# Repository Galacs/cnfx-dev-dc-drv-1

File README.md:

# CNFX Dev DC Driver 1

Dual 5V 1.5A DC motor driver for the cnfx series

## IC List

- STM32F103C8T6 (Main MCU)
- HT7533 (MCU 3v3 LDO)
- SN65HVD230DR (CAN transceiver)
- WS2812B (RGB addressable led)
- TPS259472 (+5V input efuse)
- DRV8837 (Integrated H-Bridge)

## Top preview

## Preview 3d render

## Pin definitions

```c

#define CAN_TX_PIN PA12
#define CAN_RX_PIN PA11
#define CAN_STATUS_PIN PA15

#define RGB_PIN PB13
#define ILM_PIN PB0
#define BTN_PIN PB12

#define SEL_0_PIN PB5
#define SEL_1_PIN PB6
#define SEL_2_PIN PB7

#define DC_1_SLEEP PA5
#define DC_1_IN1 PA6
#define DC_1_IN2 PA7

#define DC_1_SLEEP PA0
#define DC_1_IN1 PA1
#define DC_1_IN2 PA2
```

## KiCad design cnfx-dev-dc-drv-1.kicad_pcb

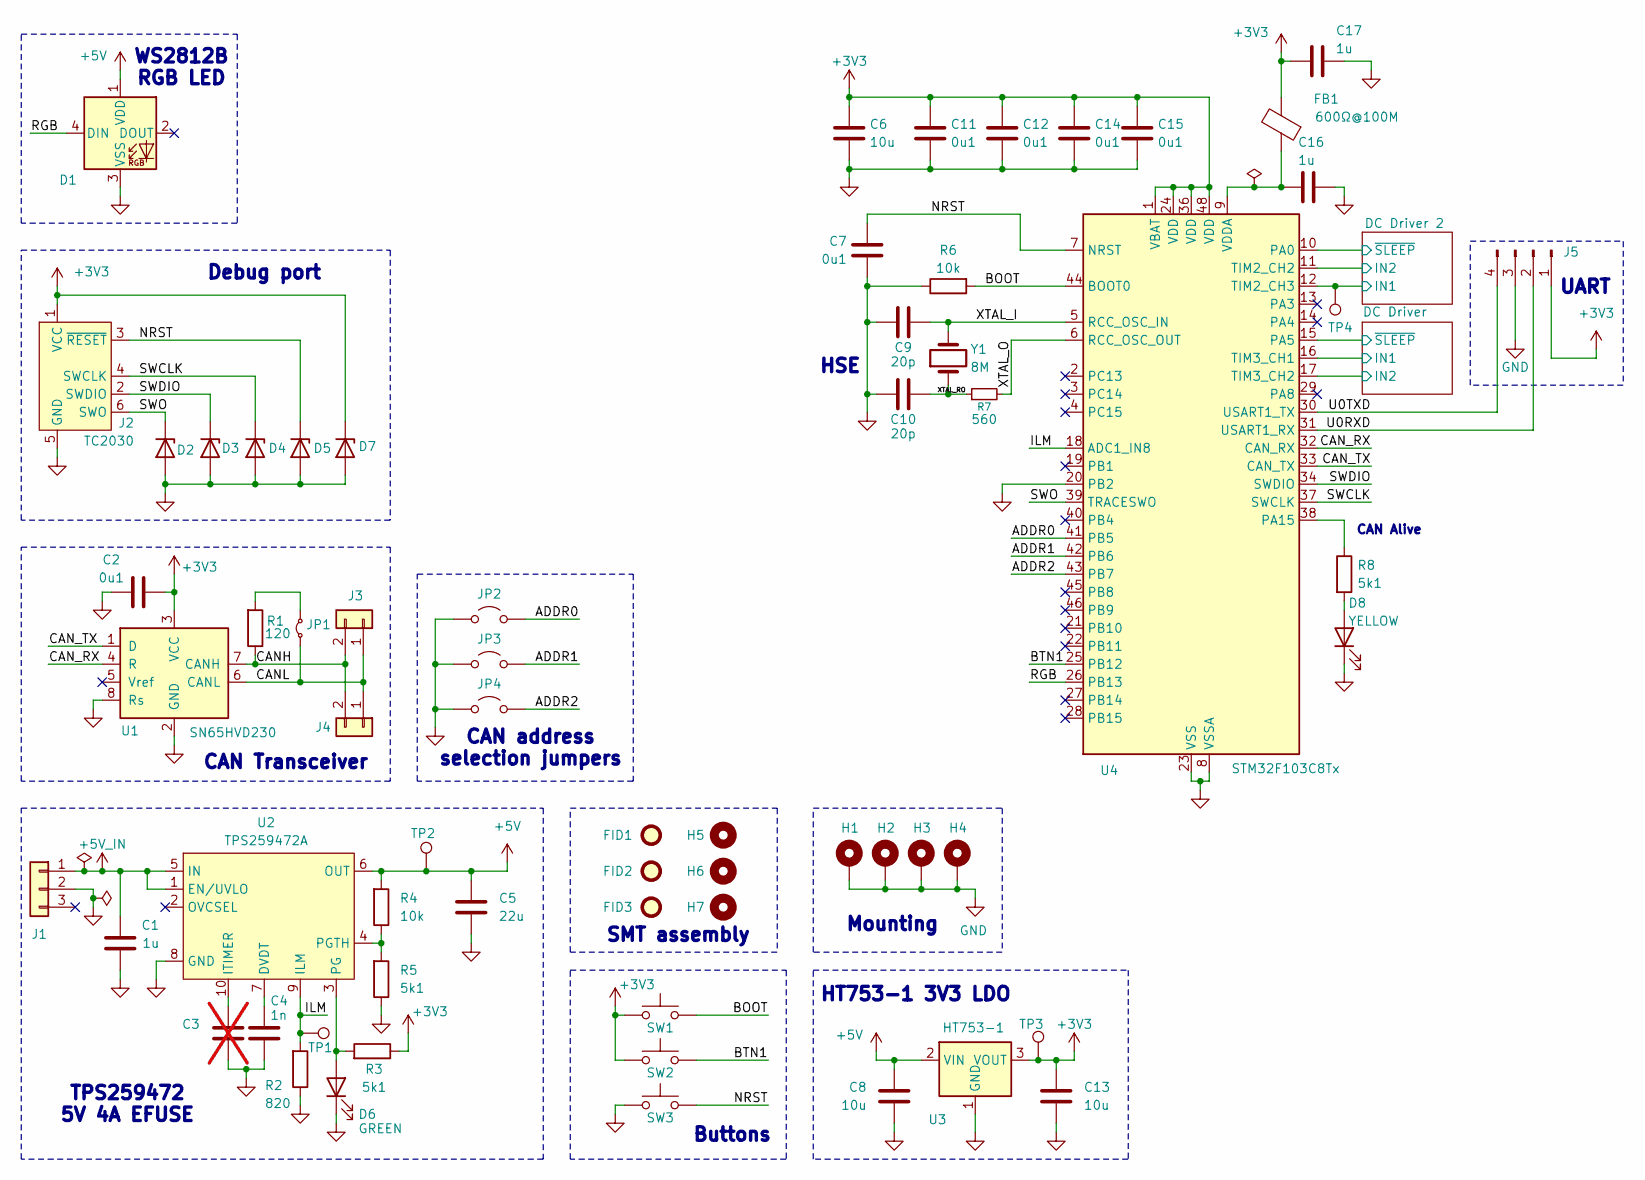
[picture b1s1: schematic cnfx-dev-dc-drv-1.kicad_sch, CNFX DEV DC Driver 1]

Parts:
C1, C16, C17: 1u; C_0402_1005Metric; Manufacturer Part Number CL05A105KA5NQNC; JLCPCB Part # C52923
C2, C7, C11, C12, C14, C15: 0u1; C_0402_1005Metric; Manufacturer Part Number CL05B104KB54PNC; JLCPCB Part # C307331
C3: C; C_0402_1005Metric; not fitted
C4: 1n; C_0402_1005Metric; Manufacturer Part Number 0402B102K500NT; JLCPCB Part # C1523
C5: 22u; C_0805_2012Metric; Manufacturer Part Number CL21A226MAQNNNE; JLCPCB Part # C45783
C6, C8, C13: 10u; C_0805_2012Metric; Manufacturer Part Number GRM21BR61H106KE43L; JLCPCB Part # C440198
C9, C10: 20p; C_0603_1608Metric; Manufacturer Part Number CL10C200JB8NNNC; JLCPCB Part # C1648
D1: WS2812B; LED_WS2812B_PLCC4_5.0x5.0mm_P3.2mm; Manufacturer Part Number WS2812B-V5/W; JLCPCB Part # C2874885
D2, D3, D4, D5, D7: H5VU10U; Diode_DFN1006; Manufacturer Part Number H5VU10U; JLCPCB Part # C22395519
D6: GREEN; LED_0805_2012Metric; Manufacturer Part Number KT-0805G; JLCPCB Part # C2297
D8: YELLOW; LED_0805_2012Metric; Manufacturer Part Number KT-0805Y; JLCPCB Part # C2296
FB1: 600Ω@100M; L_0805_2012Metric; Manufacturer Part Number MPZ2012S601ATD25; JLCPCB Part # C81034
FID1, FID2, FID3: Fiducial; Fiducial_1mm_Mask2mm
H1, H2, H3, H4: MountingHole_Pad; MountingHole_3.2mm_M3_Pad_Via
H5, H6, H7: MountingHole; ToolingHole_1.152mm
J1: Conn_01x03; JST_XH_B3B-XH-A_1x03_P2.50mm_Vertical
J2: TC2030; Tag-Connect_TC2030-IDC-NL_2x03_P1.27mm_Vertical
J3, J4: Conn_01x02; JST_XH_B2B-XH-A_1x02_P2.50mm_Vertical
J5: Conn_01x04_Pin; PinHeader_1x04_P2.54mm_Vertical
JP1: Jumper_2_Small_Bridged; PinHeader_1x02_P2.54mm_Vertical
JP2, JP3, JP4: Jumper_2_Open; SolderJumper-2_P1.3mm_Open_RoundedPad1.0x1.5mm
R1: 120; R_1206_3216Metric; Manufacturer Part Number 1206W4F1200T5E; JLCPCB Part # C17909
R2: 820; R_0402_1005Metric; Manufacturer Part Number 0402WGF8200TCE; JLCPCB Part # C25135
R3, R5, R8: 5k1; R_0402_1005Metric; Manufacturer Part Number 0402WGF5101TCE; JLCPCB Part # C25905
R4, R6: 10k; R_0402_1005Metric; Manufacturer Part Number 0402WGF1002TCE; JLCPCB Part # C25744
R7: 560; R_0603_1608Metric; Manufacturer Part Number 0603WAF5600T5E; JLCPCB Part # C23204
SW1, SW2, SW3: SW_Push; SW_SPST_TS-1088-xR020; Manufacturer Part Number TS-1088-AR02016; JLCPCB Part # C720477
TP1, TP2: TestPoint; TestPoint_Keystone_5015_Micro_Mini; Manufacturer Part Number 5015; JLCPCB Part # C2906768
TP3, TP4: TestPoint; TestPoint_Pad_D2.0mm
U1: SN65HVD230; SOIC-8_3.9x4.9mm_P1.27mm; Manufacturer Part Number SN65HVD230DR; JLCPCB Part # C12084
U2: TPS259472A; Texas_RPW0010A_VQFN-HR-10_2x2mm_P0.5mm; Manufacturer Part Number TPS259472ARPWR; JLCPCB Part # C3662789
U3: HT753-1; SOT-89-3; Manufacturer Part Number HT7533-1; JLCPCB Part # C14289
U4: STM32F103C8Tx; LQFP-48_7x7mm_P0.5mm; Manufacturer Part Number STM32F103C8T6; JLCPCB Part # C8734
Y1: 8M; Crystal_SMD_5032-2Pin_5.0x3.2mm; Manufacturer Part Number X50328MSB2GI; JLCPCB Part # C115962

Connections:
+3V3: C2.1, C6.1, C11.1, C12.1, C13.1, C14.1, C15.1, C17.1, D7.1 (K), FB1.2, J2.1 (VCC), J5.1, R3.1, SW1.1, SW2.1, TP3.1 (1_1), U1.3 (VCC), U3.3 (VOUT), U4.1 (VBAT), U4.24 (VDD), U4.36 (VDD), U4.48 (VDD); also elsewhere on the board
+5V: C5.1, C8.1, D1.1 (VDD), R4.2, TP2.1 (1_1), U2.6 (OUT), U3.2 (VIN); also elsewhere on the board
+5V_IN: C1.2, J1.1, U2.1 (EN/UVLO), U2.5 (IN)
/ADDR0: JP2.2 (B), U4.41 (PB5)
/ADDR1: JP3.2 (B), U4.42 (PB6)
/ADDR2: JP4.2 (B), U4.43 (PB7)
/BOOT: R6.2, SW1.2, U4.44 (BOOT0)
/BTN1: SW2.2, U4.25 (PB12)
/CANH: J3.2, J4.2, R1.1, U1.7 (CANH)
/CANL: J3.1, J4.1, JP1.1 (A), U1.6 (CANL)
/CAN_RX: U1.4 (R), U4.32 (CAN_RX)
/CAN_TX: U1.1 (D), U4.33 (CAN_TX)
/DC Driver 2/IN1: TP4.1 (1_1), U4.12 (TIM2_CH3); also elsewhere on the board
/DC Driver 2/IN2: U4.11 (TIM2_CH2); also elsewhere on the board
/DC Driver 2/~SLEEP: U4.10 (PA0); also elsewhere on the board
/DC Driver/IN1: U4.16 (TIM3_CH1); also elsewhere on the board
/DC Driver/IN2: U4.17 (TIM3_CH2); also elsewhere on the board
/DC Driver/~SLEEP: U4.15 (PA5); also elsewhere on the board
/ILM: R2.2, TP1.1 (1_1), U2.9 (ILM), U4.18 (ADC1_IN8)
/NRST: C7.1, D5.1 (K), J2.3 (~RESET), SW3.2, U4.7 (NRST)
/RGB: D1.4 (DIN), U4.26 (PB13)
/SWCLK: D4.1 (K), J2.4 (SWCLK), U4.37 (SWCLK)
/SWDIO: D3.1 (K), J2.2 (SWDIO), U4.34 (SWDIO)
/SWO: D2.1 (K), J2.6 (SWO), U4.39 (TRACESWO)
/U0RXD: J5.2, U4.31 (USART1_RX)
/U0TXD: J5.4, U4.30 (USART1_TX)
/XTAL_I: C9.1, U4.5 (RCC_OSC_IN), Y1.2
/XTAL_O: R7.2, U4.6 (RCC_OSC_OUT)
/XTAL_RO: C10.1, R7.1, Y1.1
GND: C1.1, C2.2, C3.2, C4.2, C5.2, C6.2, C7.2, C8.2, C9.2, C10.2, C11.2, C12.2, C13.2, C14.2, C15.2, C16.2, C17.2, D1.3 (VSS), D2.2 (A), D3.2 (A), D4.2 (A), D5.2 (A), D6.1 (K), D7.2 (A), D8.1 (K), H1.1 (1_1), H2.1 (1_1), H3.1 (1_1), H4.1 (1_1), J1.2, J2.5 (GND), J5.3, JP2.1 (A), JP3.1 (A), JP4.1 (A), R2.1, R5.1, R6.1, SW3.1, U1.2 (GND), U1.8 (Rs), U2.8 (GND), U3.1 (GND), U4.8 (VSSA), U4.20 (PB2), U4.23 (VSS), U4.35 (VSS), U4.47 (VSS); also elsewhere on the board
unnamed: D6.2 (A), R3.2, U2.3 (PG)
unnamed: D8.2 (A), R8.2
unnamed: JP1.2 (B), R1.2
unnamed: C4.1, U2.7 (DVDT)
unnamed: C3.1, U2.10 (ITIMER)
unnamed: R4.1, R5.2, U2.4 (PGTH)
unnamed: R8.1, U4.38 (PA15)
unnamed: C16.1, FB1.1, U4.9 (VDDA)

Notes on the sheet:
HSE
CAN address selection jumpers
Debug port
SMT assembly
Mounting
CAN Transceiver
UART
TPS259472 5V 4A EFUSE
HT753-1 3V3 LDO
Buttons
WS2812B RGB LED
CAN Alive

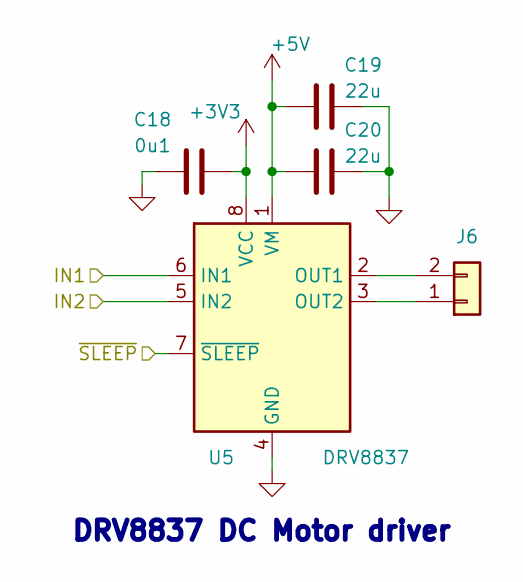
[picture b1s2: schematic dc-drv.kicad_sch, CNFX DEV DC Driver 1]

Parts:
C18: 0u1; C_0402_1005Metric; Manufacturer Part Number CL05B104KB54PNC; JLCPCB Part # C307331
C19, C20: 22u; C_0805_2012Metric; Manufacturer Part Number CL21A226MAQNNNE; JLCPCB Part # C45783
J6: Conn_01x02; JST_XH_B2B-XH-A_1x02_P2.50mm_Vertical
U5: DRV8837; WSON-8-1EP_2x2mm_P0.5mm_EP0.9x1.6mm; Manufacturer Part Number DRV8837DSGR; JLCPCB Part # C39159

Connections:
+3V3: C18.2, U5.8 (VCC); also elsewhere on the board
+5V: C19.2, C20.2, U5.1 (VM); also elsewhere on the board
/DC Driver/IN1: U5.6 (IN1); also elsewhere on the board
/DC Driver/IN2: U5.5 (IN2); also elsewhere on the board
/DC Driver/~SLEEP: U5.7 (~SLEEP); also elsewhere on the board
GND: C18.1, C19.1, C20.1, U5.4 (GND), U5.9 (GND); also elsewhere on the board
unnamed: J6.1, U5.3 (OUT2)
unnamed: J6.2, U5.2 (OUT1)

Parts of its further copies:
C21: 0u1; C_0402_1005Metric; Manufacturer Part Number CL05B104KB54PNC; JLCPCB Part # C307331
C22, C23: 22u; C_0805_2012Metric; Manufacturer Part Number CL21A226MAQNNNE; JLCPCB Part # C45783
J7: Conn_01x02; JST_XH_B2B-XH-A_1x02_P2.50mm_Vertical
U6: DRV8837; WSON-8-1EP_2x2mm_P0.5mm_EP0.9x1.6mm; Manufacturer Part Number DRV8837DSGR; JLCPCB Part # C39159

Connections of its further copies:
+3V3: C21.2, U6.8 (VCC); also elsewhere on the board
+5V: C22.2, C23.2, U6.1 (VM); also elsewhere on the board
/DC Driver 2/IN1: U6.6 (IN1); also elsewhere on the board
/DC Driver 2/IN2: U6.5 (IN2); also elsewhere on the board
/DC Driver 2/~SLEEP: U6.7 (~SLEEP); also elsewhere on the board
GND: C21.1, C22.1, C23.1, U6.4 (GND), U6.9 (GND); also elsewhere on the board
unnamed: J7.1, U6.3 (OUT2)
unnamed: J7.2, U6.2 (OUT1)

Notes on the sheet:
DRV8837 DC Motor driver

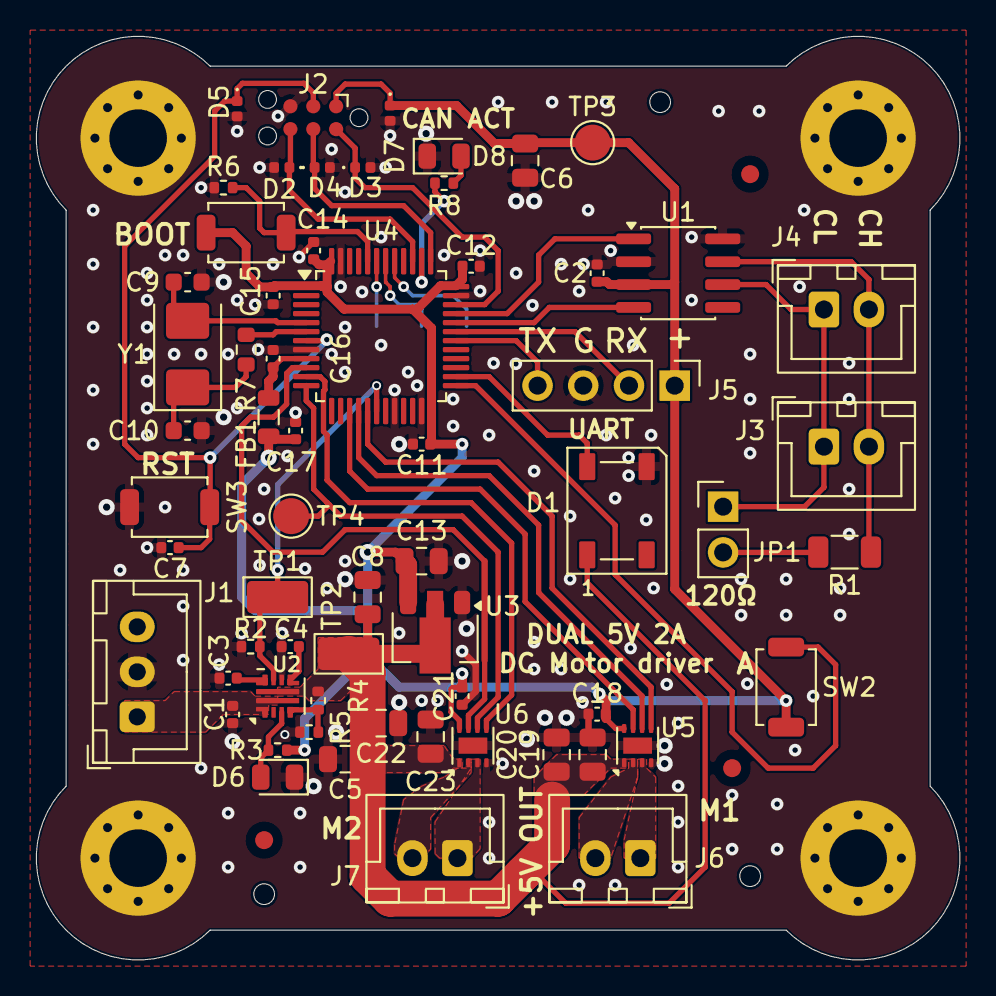
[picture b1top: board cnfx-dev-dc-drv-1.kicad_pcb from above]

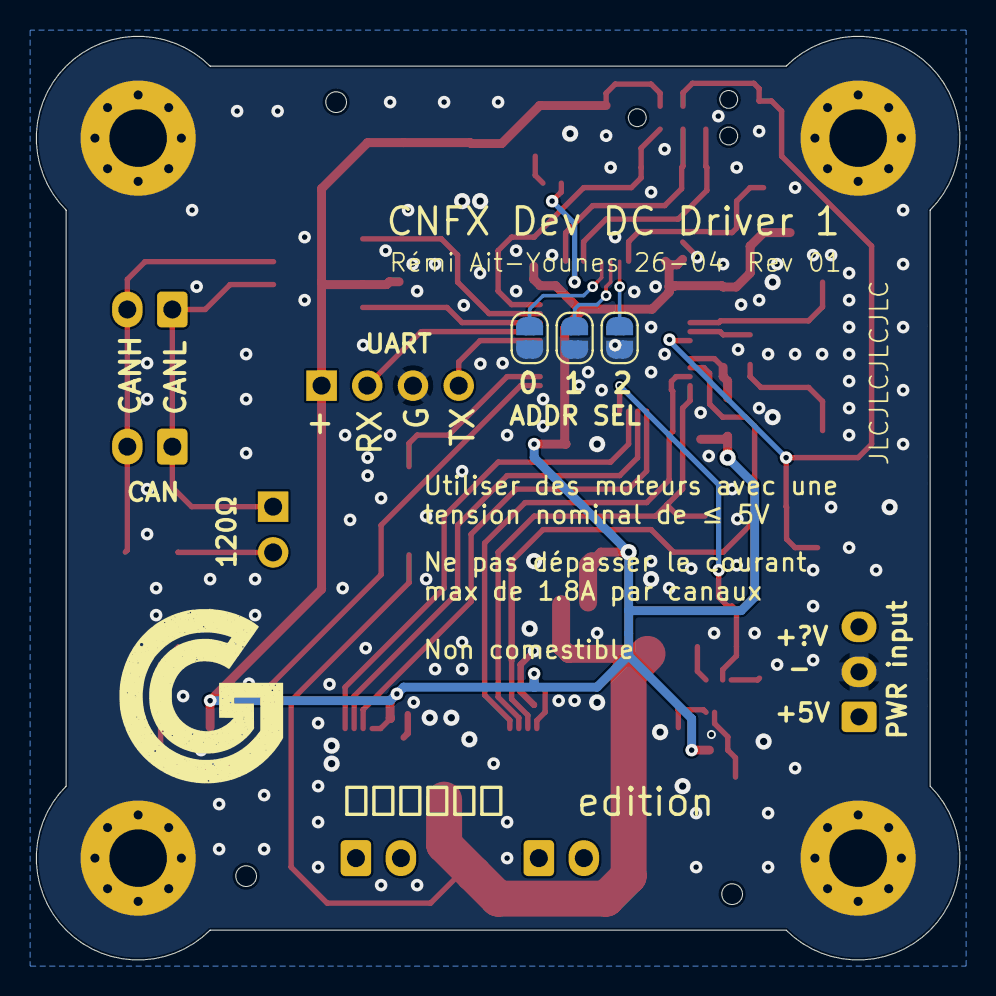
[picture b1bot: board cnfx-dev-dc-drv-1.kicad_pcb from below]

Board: 2 copper layers, 51.3 x 51.3 mm, 75 parts (3 on the bottom side), 42 nets.

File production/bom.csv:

Designator,Footprint,Quantity,Value,LCSC Part #
"C1, C16, C17",0402,3,1u,C52923
"C10, C9",0603,2,20p,C1648
"C11, C12, C14, C15, C18, C2, C21, C7",0402,8,0u1,C307331
"C13, C6, C8",0805,3,10u,C440198
"C19, C20, C22, C23",0402,4,22u,C45783
C4,0402,1,1n,C1523
C5,0805,1,22u,C45783
D1,LED_WS2812B_PLCC4_5.0x5.0mm_P3.2mm,1,WS2812B,C2874885
"D2, D3, D4, D5, D7",Diode_DFN1006,5,H5VU10U,C22395519
D6,0805,1,GREEN,C2297
D8,0805,1,YELLOW,C2296
FB1,0805,1,600Ω@100M,C81034
J1,JST_XH_B3B-XH-A_1x03_P2.50mm_Vertical,1,Conn_01x03,
"J3, J4, J6, J7",JST_XH_B2B-XH-A_1x02_P2.50mm_Vertical,4,Conn_01x02,
"JP2, JP3, JP4",SolderJumper-2_P1.3mm_Open_RoundedPad1.0x1.5mm,3,Jumper_2_Open,
R1,1206,1,120,C17909
R2,0402,1,820,C25135
"R3, R5, R8",0402,3,5k1,C25905
"R4, R6",0402,2,10k,C25744
R7,0603,1,560,C23204
"SW1, SW2, SW3",SW_SPST_TS-1088-xR020,3,SW_Push,C720477
"TP1, TP2",TestPoint_Keystone_5015_Micro_Mini,2,TestPoint,C2906768
U1,SOIC-8_3.9x4.9mm_P1.27mm,1,SN65HVD230,C12084
U2,Texas_RPW0010A_VQFN-HR-10_2x2mm_P0.5mm,1,TPS259472A,C3662789
U3,SOT-89-3,1,HT753-1,C14289
U4,LQFP-48_7x7mm_P0.5mm,1,STM32F103C8Tx,C8734
"U5, U6",WSON-8-1EP_2x2mm_P0.5mm_EP0.9x1.6mm,2,DRV8837,C39159
Y1,Crystal_SMD_5032-2Pin_5.0x3.2mm,1,8M,C115962

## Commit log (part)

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2026-04-11 schem: import STM32F103 from mhadb-2208-bldc-drv
2026-04-11 schem: add BOOT/RST and misc btns
2026-04-11 schem: import TC2030 debug connector
2026-04-11 schem: add spare gpios
2026-04-11 schem: add RGB status led
2026-04-11 schem: import CAN transceiver
2026-04-11 schem: add CAN connectors
2026-04-11 schem: add DRV8837 dc motor drivers
2026-04-11 schem: remove unused i2c pullups
2026-04-11 schem: import HT753-1 3V3 100mA LDO
2026-04-11 schem: add TPS259472 5V 4A efuse
2026-04-11 schem: change rgb led +5V supply
2026-04-11 schem: add UART connector
2026-04-11 schem: connect DC drivers to stm32
2026-04-11 schem: reorganize
2026-04-11 schem: connect rgb pin to stm32
2026-04-11 schem: fix efuse en pin
2026-04-11 schem: add test points
2026-04-11 schem: run and fix ERC
2026-04-11 schem: add ordering info to BOM
2026-04-11 schem: add title
2026-04-11 schem: reannotate
2026-04-11 pcb: create file
2026-04-11 pcb: import two layer stackup and constraints
2026-04-11 pcb: import footprints from schem
2026-04-11 schem: remove extra gpios
2026-04-11 schem: add ILM efuse reading to stm32
2026-04-11 pcb: add initial layout
2026-04-11 schem/pcb: add mounting holes
2026-04-11 pcb: refine layout
2026-04-11 pcb: add board outline
2026-04-11 pcb: add grid/place origin
2026-04-11 pcb: final layout
2026-04-11 pcb: add gnd vias
2026-04-11 pcb: add XTAL routing
2026-04-11 pcb: add SWD routing
2026-04-11 pcb: add can routing
2026-04-11 pcb: add UART routing
2026-04-11 pcb: add DC drivers routing
2026-04-11 pcb: add efuse routing
2026-04-11 pcb: add dc drivers sleep pin routing
2026-04-11 pcb: add +5V pwr routing
2026-04-11 pcb: add +3V3 pwr routing
2026-04-11 pcb: add RGB and btns routing
2026-04-11 pcb: add can status led routing
2026-04-11 pcb: add stitching vias
2026-04-11 pcb(silk): clean up reference designators
2026-04-11 pcb(silk): add user txt
2026-04-11 pcb: run and fix DRC
2026-04-11 pcb: add title
2026-04-11 generate production files
2026-04-12 schem/pcb: add smt fiducials and tooling holes
2026-04-12 schem/pcb: add can addr selection jumpers
2026-04-12 regenerate production files
2026-04-13 schem/pcb: change 22u capactior footprint
2026-04-13 schem/pcb: update dc drivers 22u bulk footprints
